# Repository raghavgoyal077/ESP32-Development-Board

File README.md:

**Compact ESP32 Development Board with USB-C, LiPo Charging, and IMU.**

` `**Power Management Design Decisions**

**Power Sources & Regulation**

- **USB-C Interface:** Provides primary 5V power supply.
- **LiPo Battery (TP4056 Module):** Secondary power source for portability.
- **Voltage Regulation:**
  - **AMS1117-3.3V:** Converts 5V from USB or ~4.2V from LiPo to 3.3V for ESP32 and peripherals.
  - **Bypass Capacitors:** 10µF capacitors placed at input/output of AMS1117 for stability.

**Power Path & Switching**

- **Schottky Diode:** Prevents reverse current flow between USB and battery.
- **Automatic Switching:** The TP4056 module allows seamless transition between USB power and battery power.
- **Battery Voltage Monitoring:** Voltage divider circuit connected to ESP32 ADC for real-time monitoring.

**Thermal Considerations**

- **Copper Pouring:** Used around AMS1117 for heat dissipation.
- **Component Placement:** AMS1117 positioned near the power input with adequate spacing to reduce heat buildup.
-----
**2. Debugging Features**

**Serial Communication for Debugging**

- **CH340G USB-to-UART Converter:** Facilitates USB serial communication.
- **Connections:**
  - **ESP32 TX → CH340G RX**
  - **ESP32 RX → CH340G TX**
  - **ESP32 IO0 → CH340G DTR** (for automatic boot mode selection)
  - **ESP32 EN (Reset) → CH340G RTS** (for automatic reset)

**Boot & Reset Controls**

- **Reset Button:** Connected to ESP32 EN pin for manual reset.
- **Boot Button:** Connected to ESP32 IO0 for manual boot mode selection.
- **Pull-up Resistors:** 10kΩ resistors on EN and IO0 for stability.

**Status Indicators**

- **Power LED:** Indicates if board is powered.
- **Charge Indicator LEDs:** Shows charging status via TP4056 module.
- **ESP32 Boot Mode LED:** Flashes when entering programming mode.

**Test Points & Expansion**

- **Exposed Test Points:** For 3.3V, GND, TX, RX, SCL, SDA, and other key signals.
- **GPIO Headers:** Allow additional peripherals to be connected.
-----
**3. PCB Layout Considerations**

**Power & Ground Planes**

- **Thicker Traces:** Used for high-current paths (~0.5mm width).
- **Dedicated Ground Plane:** Reduces noise and improves signal integrity.

**Component Placement for Debugging**

- **USB & CH340G:** Placed near board edge for easy USB access.
- **Test Points & Headers:** Clearly labelled and spaced for easy probing.

**Thermal & Noise Management**

- **AMS1117 Heat Dissipation:** Thermal vias and copper pours help manage heat.
- **Decoupling Capacitors:** Placed near power pins of ESP32 and MPU6050.
-----
**Conclusion**

This design ensures reliable power management with seamless USB/LiPo switching and efficient debugging features, making development and troubleshooting easier. Proper PCB layout techniques enhance stability and performance.

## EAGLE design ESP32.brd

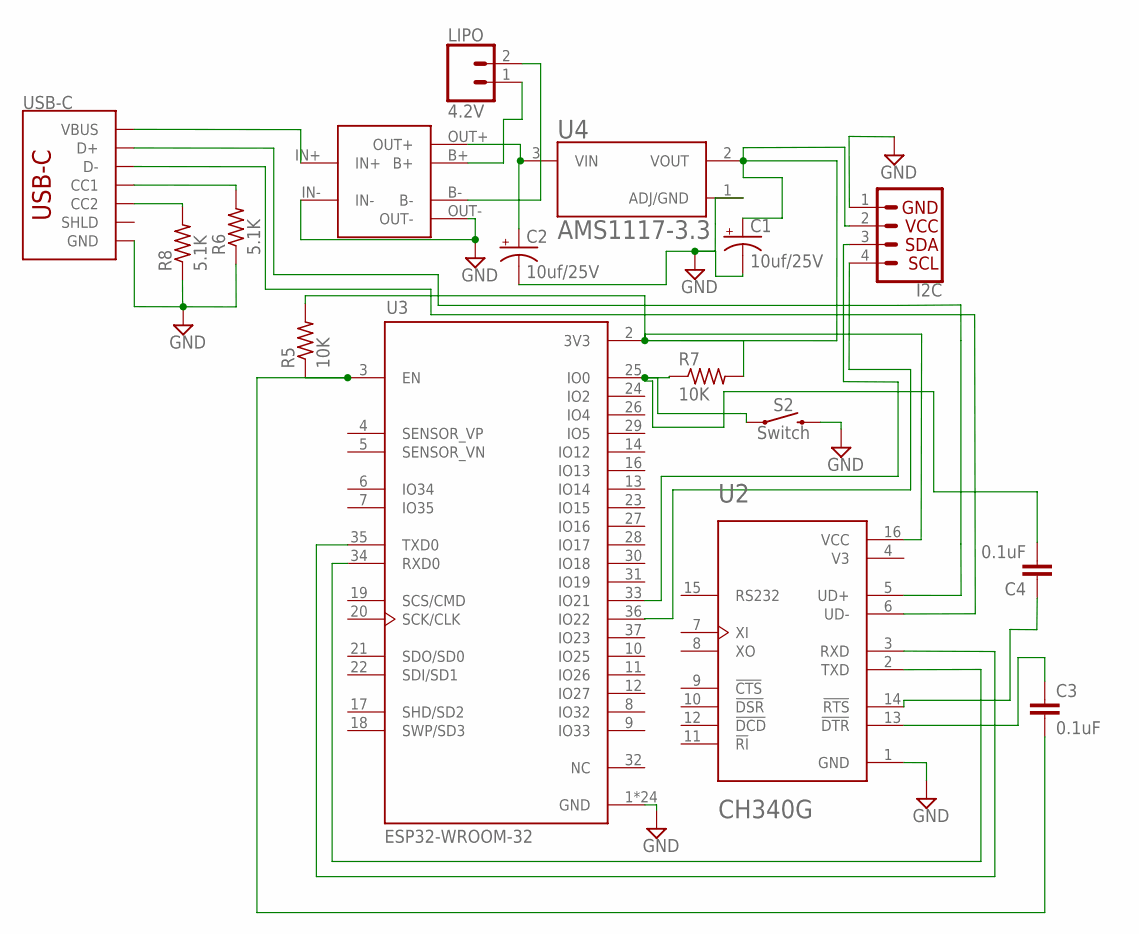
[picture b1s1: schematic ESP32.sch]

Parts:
C1, C2: 10uf/25V; CPOL-RADIAL-5MM-10MM-NS
C3, C4: 0.1uF; CAP-PTH-SMALL-KIT; MPN 20VLP10-R
I2C: I2C_STANDARD; 1X04
LIPO: 4.2V; 1X02
R5, R7: 10K; 0204/5; MPN WP4S-10KRJA2
R6, R8: 5.1K; 0204/5; MPN LR2F5K1
S2: Switch; TACTILE_SWITCH_PTH_6.0MM; MPN FSM10JH
U1: TP4056
U2: CH340G; SOIC127P600X180-16N
U3: ESP32-WROOM-32; MODULE_ESP32-WROOM-32; MPN DFR0654
U4: AMS1117-3.3; SOT229P700X180-4N
USB-C: USB_C_2-LAYER_PADS; USB-C-16P-2LAYER-PADS; MPN 105450-0101

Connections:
GND: C1.-, C2.-, I2C.1, R6.1, R8.1, S2.3 (2), U1.IN-, U1.OUT-, U2.1 (GND), U3.1 (GND), U3.15 (GND), U3.38 (GND), U3.39_1 (GND), U3.39_2 (GND), U3.39_3 (GND), U3.39_4 (GND), U3.39_5 (GND), U3.39_6 (GND), U3.39_7 (GND), U3.39_8 (GND), U3.39_9 (GND), U3.39_10 (GND), U3.39_11 (GND), U3.39_12 (GND), U3.39_13 (GND), U3.39_14 (GND), U3.39_15 (GND), U3.39_16 (GND), U3.39_17 (GND), U3.39_18 (GND), U3.39_19 (GND), U3.39_20 (GND), U3.39_21 (GND), U4.1 (ADJ/GND), USB-C.GND, USB-C.GND2 (GND)
unnamed: C1.+, I2C.2, R5.2, R7.2, U2.16 (VCC), U3.2 (3V3), U4.2 (VOUT)
unnamed: U1.IN+, USB-C.VBUS1 (VBUS), USB-C.VBUS2 (VBUS)
unnamed: C2.+, U1.OUT+, U4.3 (VIN)
unnamed: U2.5 (UD+), USB-C.A6 (D+), USB-C.B6 (D+)
unnamed: U2.6 (UD-), USB-C.A7 (D-), USB-C.B7 (D-)
unnamed: U2.3 (RXD), U3.35 (TXD0)
unnamed: U2.2 (TXD), U3.34 (RXD0)
unnamed: C3.2, R5.1, U3.3 (EN)
unnamed: C4.2, R7.1, S2.1, U3.25 (IO0)
unnamed: I2C.3, U3.33 (IO21)
unnamed: I2C.4, U3.36 (IO22)
unnamed: C3.1, U2.13 (!DTR)
unnamed: C4.1, U2.14 (!RTS)
unnamed: LIPO.1, U1.B+
unnamed: LIPO.2, U1.B-
unnamed: R6.2, USB-C.A5 (CC1)
unnamed: R8.2, USB-C.B5 (CC2)
V3: U2.4 (V3)

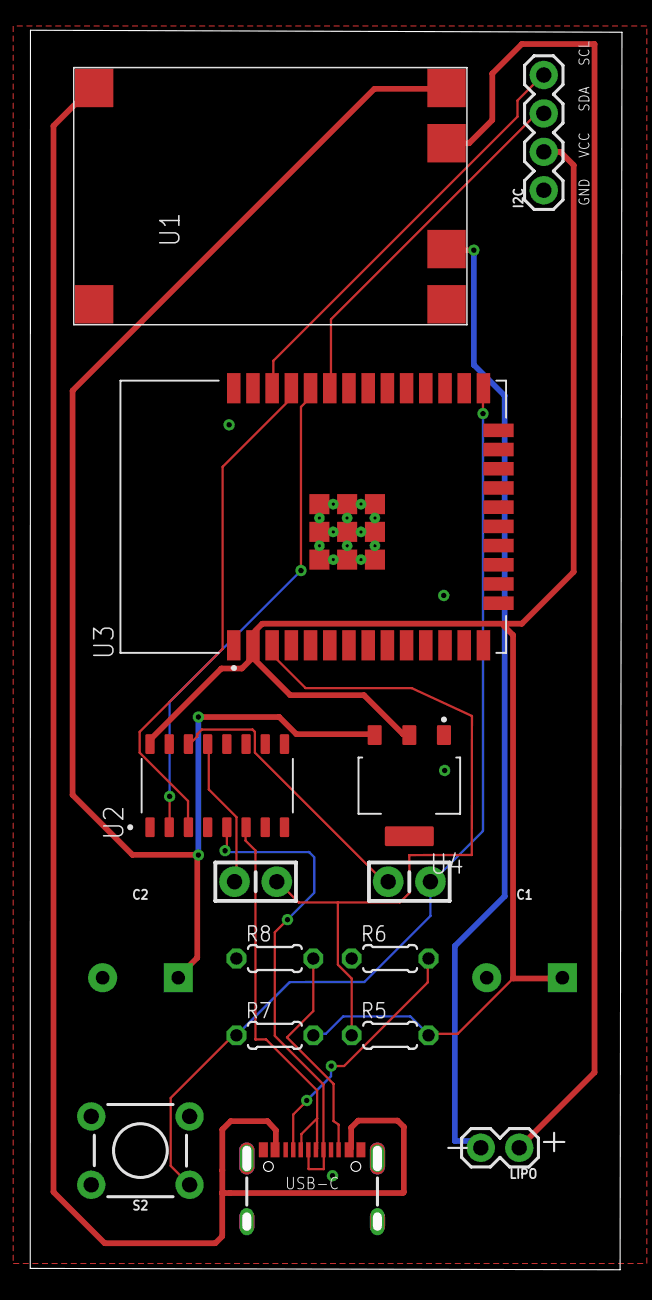
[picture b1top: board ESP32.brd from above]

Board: 2 copper layers, 38.5 x 81.4 mm, 16 parts (0 on the bottom side), 18 nets.

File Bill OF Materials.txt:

Order list for D:/New folder (2)/m.sch
Exported from EAGLE with DesignLink

Quantity	Value	Package	Order code	Manufacturer	Manuf. Code	Availability	Price (from)	Description
2	10uf/25V	CPOL-RADIAL-5MM-10MM-NS	unknown					
2	0.1uF	CAP-PTH-SMALL-KIT	2860003	VISHAY	20VLP10-R	1814	332.44	VISHAY - 20VLP10-R - Ceramic Suppression Capacitor, Y5V, Disc, 0.1 µF, ± 20%, X2, 400 V, Radial Leaded
1		1X04	unknown					
1	4.2V	1X02	unknown					
2	10K	0204/5	1219304	TT ELECTRONICS / WELWYN	WP4S-10KRJA2	457	57.97	TT ELECTRONICS / WELWYN - WP4S-10KRJA2 - Through Hole Resistor, 10 kohm, WP-S Series, 4 W, ± 5%, Axial Leaded, 100 V
2	5.1K	0204/5	2330356	NEOHM - TE CONNECTIVITY	LR2F5K1	4000	3.77	NEOHM - TE CONNECTIVITY - LR2F5K1 - Through Hole Resistor, 5.1 kohm, LR Series, 750 mW, ± 1%, Axial Leaded, 350 V
1	Switch	TACTILE_SWITCH_PTH_6.0MM	1555986	ALCOSWITCH - TE CONNECTIVITY	FSM10JH	20853	7.06	ALCOSWITCH - TE CONNECTIVITY - FSM10JH - Tactile Switch, FSMJ, Top Actuated, Through Hole, Round Button, 160 gf, 50mA at 24VDC
1	TP4056   	TP4056	unknown					
1	CH340G	SOIC127P600X180-16N	unknown					
1	ESP32-WROOM-32	MODULE_ESP32-WROOM-32	4308187	DFROBOT	DFR0654	0	1213.23	DFROBOT - DFR0654 - FireBeetle 2 Board Kit, ESP32-WROOM-32E, Xtensa LX6, 32 bit, IoT MCU
1	AMS1117-3.3	SOT229P700X180-4N	unknown					
1		USB-C-16P-2LAYER-PADS	2524076	MOLEX	105450-0101	10483	142.83	MOLEX - 105450-0101 - USB Connector, USB Type C, USB 3.1, Receptacle, 24 Ways, Surface Mount, Right Angle

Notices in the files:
parts and their libraries:
SparkFun-Capacitors: Licensing: Creative Commons ShareAlike 4.0 International - https://creativecommons.org/licenses/by-sa/4.0
